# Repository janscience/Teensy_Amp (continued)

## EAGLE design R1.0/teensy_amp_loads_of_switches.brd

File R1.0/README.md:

# TeensyAmp R1.0

by [Stefan Mucha](https://github.com/muchaste)

with support by [Avner Wallach](https://github.com/avner-wallach) and
[Jan Benda](https://github.com/janscience).

The input signals are processed in the following way:

- simple RC high-pass filtering, cutoff frequencies selectable via
  S1/S2 switches (0.1Hz, 100Hz, 300Hz)

- amplification ([Analog devices
  AD8224HACPZ-WP](https://www.analog.com/media/en/technical-documentation/data-sheets/AD8224.pdf)),
  gain selectable via S3/S4 switches (x5, x30, x180)

- low-pass filtering ([Analog devices
  OP2177ARZ](https://www.analog.com/media/en/technical-documentation/data-sheets/op1177_2177_4177.pdf)),
  cutoff frequencies selectable via S5/S6 switches (10kHz, 33kHz)

- a voltage-divider generates the 1.66V reference/ground potential ([Analog devices OP1177R](https://www.analog.com/media/en/technical-documentation/data-sheets/op1177_2177_4177.pdf))

How to configure gain and filter settings is described in
[AmplifierConfiguration.pdf](AmplifierConfiguration.pdf).

## Circuit

- [EAGLE circuit board](teensy_amp_loads_of_switches.brd)
- [EAGLE design rule](teensy_amp_loads_of_switches.dru)
- [EAGLE schematics file](teensy_amp_loads_of_switches.sch)
- [EAGLE autorouter statistics](teensy_amp_loads_of_switches.pro)

| Name1 | Name2 | Potential |
| :---- | :---- | --------: |
| VCC   | VPP   | 5V        |
| VDD   | VSS   | 0V        |
| GND1  | GND2  | 1.66V     |

## Pins

Input pins to the left, "TeensyAmp R1.0" bottom right.

### JP1 and JP2: differential inputs 1 and 2

| pin  | signal | position |
| ---: | :----  | :------- |
|    1 | IN+    | bottom   |
|    2 | IN-    | top      |

### JP3: output signals and power fowarding

| pin  | signal     | position     |
| ---: | :--------  | :----------- |
|    1 | OUT2 (JP2) | top left     |
|    2 | OUT1 (JP1) | top right    |
|    3 | VPP        | bottom left  |
|    4 | VSS        | bottom right |

- connect the amplified signals OUT1 and OUT2 to analog inputs of
  the Teensy.
- VPP and VSS could be used to power the Teensy.
- VSS does not need to be connected to AGND or GND of the Teensy!

### JP4: power input and reference generation

| pins | signal | position |
| ---: | :----- | :------- |
| 1, 2 | VCC    | top      |
| 3, 4 | VDD    | center   |
| 5, 6 | GND1   | bottom   |

- right column: VCC and VDD is used to create GND1 (1.66V).
- left column: input power and GND for the amplifier. Connected to JP5.
- when using a single amplifier,
  - connect power to both columns, in order to drive both the
    generation of the GND1 potential (right column) and the amplifier
    (left column).
  - connect the generated GND1 from the right column to GND1 of the
    left column by means of a jumper.
- additional slave amplifiers do not need to generate their GND1
  potential themselves. They receive it from the JP5 pins of the
  master amplifier on the left column of the JP4 pins.

### JP5: power forwarding

| pin  | signal      | position |
| ---: | :---------- | :------- |
|    1 | VPP = VCC   | top      |
|    2 | VSS = VDD   | center   |
|    3 | GND2 = GND1 | bottom   |

- connect these to the left column of JP4 of a another amplifier in
  order to provide power and reference. The other amplifier then does
  not need any power input to the right column of JP4.
- if only a single amplifier is used, these pins are not used.

## Filter

For selecting high- and low-pass filter settings see
[AmplifierConfiguration.pdf](AmplifierConfiguration.pdf).

### High-pass filter

| S1/S2 switch/jumper position | R1      | Ci    | tau    | fcutoff |
| :--------------------------- | ------: | ----: | -----: | ------: |
| p1 (upper jumper right)      | 100kOhm | 15uF  | 1.5s   | 0.1Hz   |
| p2 (upper jumper left)       | 100kOhm | 15nF  | 1.5ms  | 106Hz   |
| p3 (upper jumper cable left) | 100kOhm | 5.6nF | 0.56ms | 283Hz   |

### Low-pass filter

| S5/S6 switch position | fcutoff |
| :-------------------- | ------: |
| p1 (left)             |  7kHz   |
| p2 (right)            | 33kHz   |

### Filter tests

In files [`tests/filter-*.wav`](tests) a 23mV signal was sampled with
100kHz and its frequency was increased as follows: 10Hz, 12.5Hz, 16Hz,
20Hz, 25Hz, 31.5Hz, 40Hz, 50Hz, 63Hz, 80Hz, 100Hz, 125Hz, 160Hz,
200Hz, 250Hz, 315Hz, 400Hz, 500Hz, 630Hz, 800Hz, 1000Hz, 1250Hz,
1600Hz, 2000Hz, 2500Hz, 3150Hz, 4000Hz, 5000Hz, 6300Hz, 8000Hz,
10kHz, 12.5kHz, 16kHz, 20kHz.

100Hz high-pass, 7kHz low-pass:

100Hz high-pass, 33kHz low-pass:

300Hz high-pass, 33kHz low-pass:

0.1Hz high-pass, 33kHz low-pass:

These plots were generated via
```
python3 ~/Arduino/libraries/TeeRec/extras/viewwave.py -s -c 0 -t 23 -a ../tests/filter-300Hz-33kHz-gain30-23mV.wav
```

## Gains and clipping

For selecting gains see
[AmplifierConfiguration.pdf](AmplifierConfiguration.pdf).

| S3/S4 switch position | gain |
| :-------------------- | ---: |
| p1 (left)             |   x5 |
| p2 (center)           |  x30 |
| p3 (right)            | x180 |

### Gain tests

In files [`tests/gain*.wav`](tests) a sinewave of a 630Hz was
amplified and recorded with both channels.

120mV rms amplitude (340mV p-p):

23mV rms amplitude (65mV p-p):

3.8mV rms amplitude (10.7mV p-p):

Nicely amplified, with a gain that seems a bit higher than specified.

These plots were generated via
```
python3 ~/Arduino/libraries/TeeRec/extras/viewwave.py -o 0.1 -t 0.005 -g 30 -s  ../tests/gain30-23mV.wav
```

### Clipping tests

In files [`tests/clipping-gain*-*mV-step*mV.wav`](tests) the amplitude
of a 630Hz signal was increased from a start voltage in steps as
specified in the file name. Shown is the voltage as the Teensy records
it (0-3.3V).

*The signals are clipped at the bottom at about 680mV!*

This is independent on gain. Also, it does not matter whether the
amplifier is powered by 5V or 3.3V.

These plots were generated via
```
python3 ~/Arduino/libraries/TeeRec/extras/viewwave.py -s -c 0 -t 10 -r -g 1 ../tests/clipping-gain30-20mV-step1mV.wav
```

## Power consumption

### Powered by 5V (power bank)

| Configuration     | Voltage | Current | Power | Run time |
| :---------------- | ------: | ------: | ----: | -------: |
| Amplifier         | 5V      | 11.4mA  |  57mW |  543h    |
| Teensy 3.5        | 5V      |  75mA   | 370mW |   82h    |
| Teensy + SD       | 5V      | 103mA   | 515mW |   60h    |
| Teensy + Amp      | 5V      |  87mA   | 433mW |   71h    |
| Teensy + Amp + SD | 5V      | 115mA   | 575mW |   54h    |

The last colum is the run time to be expected for a 10Ah battery (10Ah
times 3.7V LiPo voltage divided by 5.1V output voltage times 85%
efficiancy (=0.62) divided by current).

The amplifier takes just 11.5mA (57mW).

The Teensy consumes about seven to ten (with SD card writes) times
more power than the amplifier.

If we want to cut power consumption, we need to cut it on the Teensy!

### Powered by 3.3V

| Configuration     | Voltage | Current | Power |
| :---------------- | ------: | ------: | ----: |
| Amplifier         | 3.3V    | 6.5mA   |  21mW |
| Teensy 3.5        | 3.3V    |  68mA   | 225mW |
| Teensy + SD       | 3.3V    |  96mA   | 315mW |
| Teensy + Amp      | 3.3V    |  75mA   | 249mW |
| Teensy + Amp + SD | 3.3V    | 102mA   | 336mW |

This cuts down power consumption by almost a factor of two.  We should
power the system directly from the LiPo battery and not over the 5V
USB voltage.

## SD write artifacts

The files [`tests/sdwrites-gain*.wav`](tests) recorded 10s of
short-circuited inputs (zero signal).

With a sampling rate of 44kHz and two channels, an SD write occurs
every almost 200ms. This is visible in the traces as elevated noise
levels for about 2ms.

What is the reason for the irregularly appearing dips in the voltage?

These plots were generated via
```
python3 ~/Arduino/libraries/TeeRec/extras/viewwave.py -s -a -o 0.37 -t 0.03 ../tests/sdwrites-gain180-zero.wav
```

## Noise

Standard deviations in raw integers for each channel.

### 100kHz sampling rate, 12bit, 100Hz high-pass, 7kHz low pass, x30 gain

| convers  | sampling | avrg |   A1 |   A2 |
| :------- | :------- | ---: | ---: | ---: |
| veryhigh | veryhigh |    1 |  3.0 |  2.9 |
| veryhigh | veryhigh |    4 |  6.6 |  6.8 |
| veryhigh | veryhigh |    8 |  2.1 |  2.3 |
| veryhigh | high     |    1 |  4.5 |  4.4 |
| veryhigh | high     |    4 |  1.7 |  3.1 |
| veryhigh | high     |    8 |  5.4 |  5.8 |
| veryhigh | med      |    1 |  2.5 |  2.2 |
| veryhigh | med      |    4 |  3.3 |  3.5 |
| veryhigh | med      |    8 |  2.5 |  2.9 |
| veryhigh | low      |    1 |  5.9 |  5.9 |
| veryhigh | low      |    4 |  3.0 |  3.0 |
| veryhigh | low      |    8 |  4.6 |  4.6 |
| veryhigh | verylow  |    1 |  3.5 |  3.1 |
| veryhigh | verylow  |    4 |  1.9 |  1.8 |
| high     | veryhigh |    1 |  6.2 |  6.2 |
| high     | veryhigh |    4 |  4.8 |  4.9 |
| high     | high     |    1 |  6.1 |  6.0 |
| high     | high     |    4 |  1.6 |  1.6 |
| high     | med      |    1 |  2.8 |  2.7 |
| high     | med      |    4 |  4.2 |  4.3 |
| high     | low      |    1 |  4.9 |  4.8 |
| high     | low      |    4 |  1.7 |  1.7 |
| high     | verylow  |    1 |  4.0 |  4.0 |
| med      | veryhigh |    1 |  5.8 |  5.9 |
| med      | high     |    1 |  2.9 |  3.0 |
| med      | med      |    1 |  4.5 |  4.6 |
| med      | low      |    1 |  2.8 |  2.7 |
| med      | verylow  |    1 |  4.7 |  4.8 |

A good setting:

A bad setting:

### 20kHz sampling rate, 12bit, 100Hz high-pass, 7kHz low pass, x30 gain

| convers  | sampling | avrg |   A1 |   A2 |
| :------- | :------- | ---: | ---: | ---: |
| veryhigh | veryhigh |    1 |  3.3 |  3.3 |
| veryhigh | veryhigh |    4 |  4.2 |  3.1 |
| veryhigh | veryhigh |    8 |  1.9 |  1.9 |
| veryhigh | veryhigh |   16 |  3.5 |  3.8 |
| veryhigh | veryhigh |   32 |  1.9 |  1.8 |
| veryhigh | high     |    1 |  3.1 |  3.1 |
| veryhigh | high     |    4 |  2.5 |  2.4 |
| veryhigh | high     |    8 |  2.4 |  2.3 |
| veryhigh | high     |   16 |  2.8 |  1.9 |
| veryhigh | high     |   32 |  1.7 |  2.8 |
| veryhigh | med      |    1 |  3.4 |  3.5 |
| veryhigh | med      |    4 |  2.3 |  2.0 |
| veryhigh | med      |    8 |  1.7 |  1.5 |
| veryhigh | med      |   16 |  3.0 |  2.9 |
| veryhigh | med      |   32 |  1.9 |  2.0 |
| veryhigh | low      |    1 |  2.7 |  2.8 |
| veryhigh | low      |    4 |  2.0 |  2.0 |
| veryhigh | low      |    8 |  4.0 |  4.0 |
| veryhigh | low      |   16 |  1.4 |  1.3 |
| veryhigh | low      |   32 |  1.3 |  1.4 |
| veryhigh | verylow  |    1 |  3.3 |  3.1 |
| veryhigh | verylow  |    4 |  2.0 |  2.0 |
| veryhigh | verylow  |    8 |  1.4 |  1.4 |
| veryhigh | verylow  |   16 |  1.8 |  1.8 |
| veryhigh | verylow  |   32 |  2.7 |  2.1 |
| high     | veryhigh |    1 |  3.1 |  2.7 |
| high     | veryhigh |    4 |  2.1 |  2.0 |
| high     | veryhigh |    8 |  2.5 |  2.5 |
| high     | veryhigh |   16 |  1.4 |  1.4 |
| high     | veryhigh |   32 |  3.0 |  2.7 |
| high     | high     |    1 |  3.6 |  3.2 |
| high     | high     |    4 |  2.3 |  2.2 |
| high     | high     |    8 |  1.4 |  1.3 |
| high     | high     |   16 |  2.0 |  2.0 |
| high     | med      |    1 |  3.3 |  3.1 |
| high     | med      |    4 |  2.0 |  2.0 |
| high     | med      |    8 |  1.4 |  1.4 |
| high     | med      |   16 |  1.7 |  1.8 |
| high     | low      |    1 |  6.1 |  6.1 |
| high     | low      |    4 |  1.5 |  1.5 |
| high     | low      |    8 |  2.2 |  2.1 |
| high     | low      |   16 |  3.0 |  2.8 |
| high     | verylow  |    1 |  3.3 |  3.1 |
| high     | verylow  |    4 |  1.9 |  1.9 |
| high     | verylow  |    8 |  2.2 |  2.2 |
| high     | verylow  |   16 |  2.3 |  2.3 |
| med      | veryhigh |    1 |  2.4 |  2.3 |
| med      | veryhigh |    4 |  2.3 |  2.3 |
| med      | veryhigh |    8 |  2.1 |  2.1 |
| med      | veryhigh |   16 |  1.2 |  1.2 |
| med      | high     |    1 |  3.2 |  2.9 |
| med      | high     |    4 |  2.4 |  2.3 |
| med      | high     |    8 |  1.5 |  1.4 |
| med      | high     |   16 |  2.2 |  2.2 |
| med      | med      |    1 |  3.1 |  3.1 |
| med      | med      |    4 |  6.4 |  6.4 |
| med      | med      |    8 |  1.5 |  1.5 |
| med      | low      |    1 |  3.4 |  3.2 |
| med      | low      |    4 |  3.6 |  2.8 |
| med      | low      |    8 |  1.3 |  1.3 |
| med      | verylow  |    1 |  2.5 |  2.4 |
| med      | verylow  |    4 |  2.1 |  2.1 |
| med      | verylow  |    8 |  2.0 |  2.0 |

A good setting:

A bad setting:

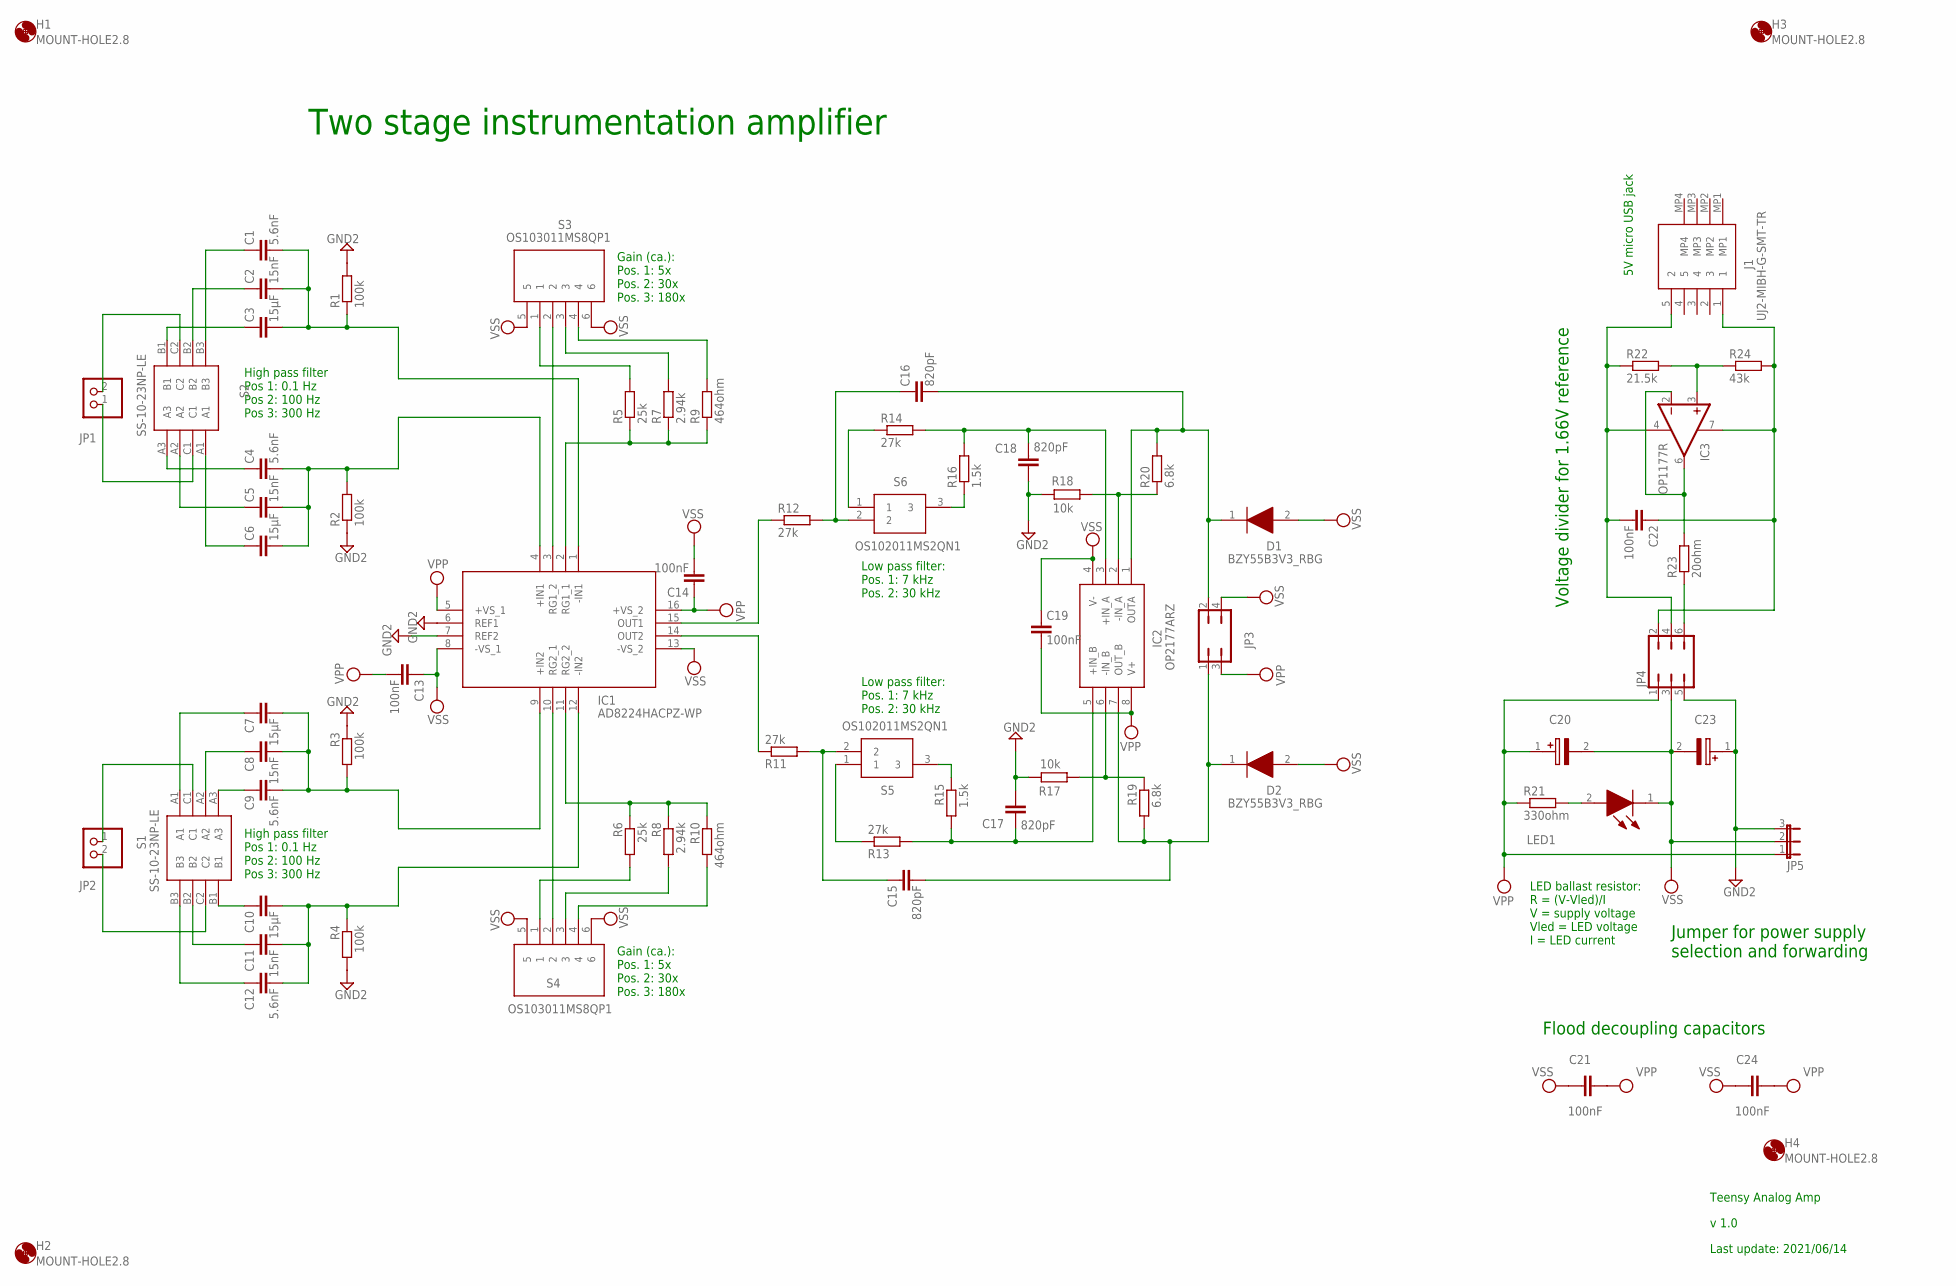
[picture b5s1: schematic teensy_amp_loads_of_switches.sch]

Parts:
C1, C4, C9, C12: 5.6nF; C0805
C2, C5, C8, C11: 15nF; C0805
C3, C6, C7, C10: 15µF; C0805
C13, C14, C19, C21, C22, C24: 100nF; C0805
C15, C16, C17, C18: 820pF; C0805
C20, C23: TAJA475K010RNJV; CAPPM3216X180N
D1, D2: BZY55B3V3_RBG; BZY55B3V3RBG
H1, H2, H3, H4: MOUNT-HOLE2.8; 2,8
IC1: AD8224HACPZ-WP; QFN65P400X400X100-16N
IC2: OP2177ARZ; SOIC127P600X175-8N
IC3: OP1177R; SOIC8
J1: UJ2-MIBH-G-SMT-TR; UJ2MIBHGSMTTR
JP1, JP2: PINHD-1X2; 1X02
JP3: JP2Q
JP4: JP3Q
JP5: JP2E; JP2
LED1: 150060RS75000; LEDC1608X80N
R1, R2, R3, R4: 100k; R0805
R5, R6: 25k; R0805
R7, R8: 2.94k; R0805
R9, R10: 464ohm; R0805
R11, R12, R13, R14: 27k; R0805
R15, R16: 1.5k; R0805
R17, R18: 10k; R0805
R19, R20: 6.8k; R0805
R21: 330ohm; R0805
R22: 21.5k; R0805
R23: 20ohm; R0805
R24: 43k; R0805
S1, S2: SS-10-23NP-LE; SS1023NPLE
S3, S4: OS103011MS8QP1
S5, S6: OS102011MS2QN1; OS102011MA1QN1

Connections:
GND2: C17.2, C18.2, C23.1 (+), IC1.6 (REF1), IC1.7 (REF2), JP4.5, JP5.3, R1.2, R2.1, R3.1, R4.2, R17.2, R18.2
unnamed: JP1.2, S2.C2
unnamed: JP1.1, S2.C1
unnamed: C16.1, R12.2, S6.2
unnamed: C4.1, S2.A3
unnamed: C5.1, S2.A2
unnamed: C6.1, S2.A1
unnamed: LED1.2 (A), R21.2
unnamed: C22.2, IC3.4 (V-), J1.5 (2), JP4.4, R22.1
unnamed: IC3.3 (+IN), R22.2, R24.1
unnamed: IC3.2 (-IN), IC3.6 (OUT), R23.2
unnamed: C22.1, IC3.7 (V+), J1.1, JP4.2, R24.2
unnamed: C3.1, S2.B1
unnamed: C1.1, S2.B3
unnamed: C4.2, C5.2, C6.2, IC1.4 (+IN1), R2.2
unnamed: C1.2, C2.2, C3.2, IC1.1 (-IN1), R1.1
unnamed: C2.1, S2.B2
unnamed: IC1.3 (RG1_2), S3.2
unnamed: IC1.15 (OUT1), R12.1
unnamed: IC2.2 (-IN_A), R18.1, R20.1
unnamed: C11.1, S1.B2
unnamed: C18.1, IC2.3 (+IN_A), R14.2, R16.2
unnamed: R6.2, S4.1
unnamed: R8.2, S4.3
unnamed: R10.2, S4.4
unnamed: IC1.11 (RG2_2), R6.1, R8.1, R10.1
unnamed: JP2.2, S1.C2
unnamed: JP2.1, S1.C1
unnamed: C9.1, S1.A3
unnamed: R5.2, S3.1
unnamed: R7.2, S3.3
unnamed: R9.2, S3.4
unnamed: IC1.2 (RG1_1), R5.1, R7.1, R9.1
unnamed: C8.1, S1.A2
unnamed: C7.1, S1.A1
unnamed: C10.1, S1.B1
unnamed: C12.1, S1.B3
unnamed: C7.2, C8.2, C9.2, IC1.9 (+IN2), R3.2
unnamed: C10.2, C11.2, C12.2, IC1.12 (-IN2), R4.1
unnamed: IC1.10 (RG2_1), S4.2
unnamed: JP4.6, R23.1
unnamed: R14.1, S6.1
unnamed: C16.2, D1.1 (K), IC2.1 (OUTA), JP3.2, R20.2
unnamed: R16.1, S6.3
unnamed: IC1.14 (OUT2), R11.1
unnamed: C17.1, IC2.5 (+IN_B), R13.2, R15.2
unnamed: IC2.6 (-IN_B), R17.1, R19.1
unnamed: C15.2, D2.1 (K), IC2.7 (OUT_B), JP3.1, R19.2
unnamed: R13.1, S5.1
unnamed: C15.1, R11.2, S5.2
unnamed: R15.1, S5.3
VPP: C13.2, C14.1, C19.2, C20.1 (+), C21.2, C24.2, IC1.5 (+VS_1), IC1.16 (+VS_2), IC2.8 (V+), JP3.3, JP4.1, JP5.1, R21.1
VSS: C13.1, C14.2, C19.1, C20.2 (-), C21.1, C23.2 (-), C24.1, D1.2 (A), D2.2 (A), IC1.8 (-VS_1), IC1.13 (-VS_2), IC2.4 (V-), JP3.4, JP4.3, JP5.2, LED1.1 (K), S3.5, S3.6, S4.5, S4.6

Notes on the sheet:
High pass filter Pos 1: 0.1 Hz Pos 2: 100 Hz Pos 3: 300 Hz
Gain (ca.): Pos. 1: 5x Pos. 2: 30x Pos. 3: 180x
Low pass filter: Pos. 1: 7 kHz Pos. 2: 30 kHz
Flood decoupling capacitors
5V micro USB jack
Jumper for power supply selection and forwarding
LED ballast resistor: R = (V-Vled)/I V = supply voltage Vled = LED voltage I = LED current
Teensy Analog Amp
v 1.0
Last update: 2021/06/14
Voltage divider for 1.66V reference
Two stage instrumentation amplifier

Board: 2 copper layers, 70 parts (2 on the bottom side), 53 nets, no tracks yet.

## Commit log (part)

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2021-11-15 Initial upload of pictures and schematics
2021-11-20 added teensy amp switches PCB.png
2021-11-20 READMEs for two revisions of the amp
2021-11-20 fixed pin markdown
2021-11-20 moved files to R1.0
2021-11-20 removed spaces from file names
2021-11-20 cropped images
2021-11-20 links to ICs
2021-11-20 added filter measurements
2021-11-20 added noise tests
2021-11-21 added clipping tests
2021-11-21 added sdwrite artifacts
2021-11-21 hint for low voltage clipping
2021-11-22 improved clipping plots
2021-11-22 more comments on clipping
2021-11-22 added 300Hz high-pass filter test
2021-11-22 added gain test data
2021-11-22 added gain examples
2021-11-22 organized R2 todos
2021-11-22 improved README
2021-11-22 some fixes
2021-11-23 Documentation for R1 amp configuration
2021-11-23 R1 picture added
2021-11-23 improved description of pin assignment
2021-11-23 larger pins image
2021-11-23 pins image further below
2021-11-24 more details on pins
2021-11-29 fixed runtime estimates
2021-11-29 added explanation to run time estimate
2022-04-30 [R2.0] new comments on 3.3V power supply
2022-05-10 comment on new OP amps for R2
2022-05-23 added link to fishfinder
2022-06-17 R3.0
2022-06-20 [R3.0] more gains
2022-06-28 [R3.0] circuit documentation
2022-06-28 [R3.0] cropped pcb
2022-06-29 [R3.0] added noise test for 441.kHz
2022-06-29 [R3.0] added noise test for 441.kHz and gain of 50
2022-06-29 [R3.0] new noise test for 441.kHz and gain of 50
2022-06-29 [R3.0] new sdwrites for gain of 50
2022-06-29 [R3.0] restored pcb description
2022-07-02 [R3] more capacities for highpass
2022-07-09 [R3.0] added images
2023-01-10 [R3] first tests of improved version
2023-01-10 [R3] added images of noise tests
2023-01-10 [R3] fixed images of noise tests
2023-01-13 [R3] sdwrite measurement with ldoaref
2023-01-14 a few more measurements
2023-01-14 documented sdwrite experiments
2023-01-16 [R3] removed R3 resistance from Teensy
2023-01-19 [R3] further tests with different higphpass and sampling rate
2023-01-19 [R3] updated 400kHz test
2023-01-20 [R3] externa power tests
2023-01-20 [R3] external power tests fixed image include
2023-01-21 more ideas in README
2023-01-23 [R3] new measurements
2023-01-23 [R3] test image arrangement
2023-01-23 [R3] test image arrangement 2
2023-01-23 [R3] test image arrangement 3
2023-01-24 [R3] added test with AGND
2023-01-25 [R3] clipping, filter and a gain test
2023-01-25 [R3] gain tests
2023-01-25 [R3] noise test at x870
2023-01-26 [R3] noise test at intermediate gains
2023-01-26 [R3] control sinewave
2023-01-26 [R3] sdwrite noise measured externally
2023-01-26 [R3] added conclusions to tests
2023-01-26 [R3] fixes
2023-02-01 [R3] fixed channel naming
2023-03-18 fixed image links
2023-04-04 [R4] more background infos
2023-04-05 [R4] 8 versus 16 channel
2023-06-07 updated power consumption
2023-06-21 pins
2023-06-27 notes on how to proceed with EVM
2023-06-28 gains and amplitudes
2023-07-02 [R4] added notes
2023-07-04 preamp
2023-07-04 preamp capacitors
2023-07-04 fixed preamp layout
2023-07-04 preamp with 220nF
2023-07-04 filter
2023-07-04 vref buffer
2023-07-04 small fixes
2023-07-06 updated pins
2023-07-06 push button
2023-07-06 fixed filter
2023-07-06 fixed preamp
2023-07-07 new measurements with properly windowed spectra
2023-07-07 fixed spectra
2023-07-07 fixed README
2023-07-07 fix spectra 2
2023-07-07 IO pins
2023-07-07 preamp and preampinv
2023-07-10 no lowpass necessary
2023-07-10 updated circuit
2023-07-10 added circuit
2023-07-10 highpass filter tests
2023-07-10 explored 40dB gain
2023-07-10 low pass at different gains
2023-07-10 low pass with 1 Ohm
2023-07-17 added eagle files
2023-07-17 cleaned up R4
2023-07-17 [R4] variants for components to test
2023-07-17 [R4] number of parts
2023-07-18 added pcb image
2023-07-28 [R4] 8 channel test
2023-07-28 [R4] fixed image link
2023-07-28 [R4] noise tests
2023-07-28 [R4] fixed noise image names
2023-07-28 [R4] added nonlinearity measurements of signal filter
2023-07-31 updated overview
2023-07-31 added clipping
2023-07-31 clipping tests
2023-07-31 fixing preamp tests
2023-08-01 [R4] evaluation
2023-08-01 [R4] improved spectra plots
2023-08-01 [R4] low-pass filter tests
2023-08-01 [R4] high-pass filter tests with preamp
2023-08-01 [R4] high-pass filter fix
2023-08-01 [R4] low-pass filter without preamp
2023-08-01 [R4] low-pass filter without preamp added images
2023-08-01 [R4] high-pass filter without preamp
2023-08-01 updated filter and preamp circuits
2023-08-02 circuit for 10x gain
2023-08-03 [R4] renamed variants to variants1
2023-08-03 [R4] added variants2
2023-08-03 [R4] linearity tests for variant2
2023-08-03 [R4] filter tests for variant2
2023-08-07 [R4] preamp with R1=100k
2023-08-07 [R4] filter with R1=100k
2023-08-07 [R4] filter with R1=1k
2023-08-07 [R4] updated filter circuit
2023-08-07 [R4] updated preamp circuits
2023-08-07 [R4.1] added R4.1
2023-08-07 [R4.1] fixed preaminv circuit
2023-08-07 [R4.1] explained circuit
2023-08-07 [R4.0] added filter measurements with low-pass
2023-08-07 [R4.0] fixed filter measurements with low-pass
2023-08-07 [R4.0] updated filter circuit
2023-08-07 [R4.0] updated preamp circuit
2023-08-08 [R4.0] measured power consumption
2023-08-09 [R4.0] fixed pins
2023-08-10 [R4] fixed pins
2023-08-10 [R4] improved pinouts
2023-08-11 [R4] 16 channels
2023-08-11 [R4] 16 channels in sync
2023-08-11 [R4.1] pinout
2023-08-15 dimensions
2023-08-15 [R4.1] pin update
2023-08-17 R4.2 circuits
2023-08-17 [R4.2] LED pin on 27
2023-08-17 added 4.1 to main page
2023-08-17 fixes
2023-08-18 [R40] image of board
2023-08-18 [R40] fixed image link
2023-09-08 [R4] added pcm1865 data sheet
2023-09-09 added images for the new R4.1 and R4.2 PCBs
2023-09-10 annotated R41 and R42 images
2023-09-11 updated R40 annotation
2023-09-11 added preamp tests
2023-09-11 filter measurement on single channel
2023-09-12 [R4.0] updated linearity spectra
2023-09-12 [R4.0] added OPA1622 data sheet
2023-09-15 [R4.0] CAN I/O in and out pins
2023-09-16 [R4.1] fixed IO pins
2023-09-16 [R4] fixed eagle links
2023-09-16 [R4] added TCAN data sheet
2023-09-16 [R4] CAN bus needs to be terminated
2023-10-21 sugestions for improving R41. and R4.2
2024-08-02 added missing pdfs
2024-08-02 [R4.2] added missing jpg
2024-08-02 [R4.1] added missing jpg
2024-08-02 [R4.1-R4.2] added missing jpgs
2024-08-02 [R4.x] fixed docs
2024-08-02 [R5.0] infos on the TI chip
2024-08-06 [R4.x] updated docs
2024-08-07 [R4.x] added pinput images
2024-08-07 [R4.1b] added pinout image
2024-08-07 [R4.1b] fixed pinout link
2024-08-07 [R4.1b] changed pdf to svg
2024-08-07 [R4.1b] added VBAT
2024-08-08 [R4.0] moved PCB image to README
2024-08-08 [doc] updated use cases
2024-08-10 [doc] link to TeeRec
2024-08-10 [R4.2b] added pinout desciption
2024-08-10 [R4.2b] removed VBAT
2024-08-10 [R4.1b] comment on DIP switches for device ID
2024-08-12 [R4.1b] update on device ID dips
2024-08-13 [R4.1b] added layout
2024-08-13 [R4.1b] added coin battery type
2024-08-13 [R4.1b] added preamp sketch and gain
2024-08-13 [R4.1b] moved DIP switch to other side
2024-08-13 [R4.1b] update
2024-08-13 [R4.2b] fixed title
2024-09-09 [R4.1b] new specs
2024-09-10 [R4.1] added links to isolated CAN bus chips
2024-09-10 [R4.1] added SD cards and USB ports to layout
2024-09-10 [R4.1] CAN bus back in Teensy pinput
2024-09-11 [R4.0] added data rates and SD speed class
2024-09-14 [R4.0] link to data rates tables in TeeRec
2024-09-15 [R4.1] only one external SD card slot
2024-09-15 [R4.1] description of device ID dip switches
2024-09-15 [R4.1] added DIP power to pinout
2024-09-15 [R4.1] fixed text
2024-09-30 [R4.1b] updated details on external devices, inclusively backup SD card
2024-10-01 [R4.1b] added notes on power switch, push-button and on-board temperature sensor
2024-10-01 [R4.1b] fixes
2024-10-01 [R4.1b] added isolated CAN bus
2024-10-01 [R4.1b] turned pinpout
2024-10-01 [R4.1b] updated layout
2024-10-01 [R4.1b] temperature sensor
2024-10-02 [R4.1b] improved pin colors
2024-10-02 [R4.1b] link out to IC drawings
2024-10-02 [R4.1b] specified connectors
2024-10-02 [R4.1] note on larger PCB dimensions
2024-10-02 [R4.1] small improvements
2024-10-11 [R4.1] added notes on rotary DIP switch and yet another temperature sensor
2024-11-05 powerbank runtime
2024-11-22 [R4.1] add real-time clock to PCB
2024-11-25 [R4.1-R4.2] added more power measurements
2024-11-25 [R4.1+R4.2] script for analysing power consumption
2024-11-27 [powerconsumption] compute averages
2024-11-27 [doc] added infos to power banks
2024-12-20 [docs] more power consumption measurements
2024-12-21 evaluated power consumption
2024-12-21 removed brand from tables
2025-01-17 [R4.1] notes on isolation tests
2025-01-18 [R4.1] note on real time clocks
2025-01-23 [R41] alternative connectors
2025-01-24 [R41] test measurements for grid configuration
2025-01-24 [R4.1] added analysis of power tests
2025-01-25 [R4.1] added note on low-pass filter
2025-01-27 [R4.1] added power test ananlysis
2025-01-27 [R4.1] fixed power test
2025-01-27 [R4.1] improved calculations
2025-04-07 hint for small 10Ah powerbank
2025-06-04 [R4.1] updated new design
2025-07-01 [R4.1b] updated RTC
2025-07-06 [R4.1b] added parts
2025-07-07 [R41] added parts
2025-07-09 [R41] added rotary switch
2025-07-10 [R41] added note on slide switch
2025-07-11 [R4.1b] another power switch
2025-07-12 [R4.1b] yet another power switch
2025-07-13 [R4.1b] finalized
2025-07-15 opa1662 is the op amp
2025-10-20 [R4.2b] updated docs to new version
2025-10-20 [R4.1b] updated docs to new version
2025-10-20 [R4.1b-R4.2b] updated docs to new version
2025-10-22 [R41] uodated layout image
2025-10-22 [R41] updated docu
2025-10-22 [R4142] updated docu
2025-10-28 [R4.1c] without onewire bus
2025-10-29 [R4.1-R4.2] added power consumption
2025-10-30 [R4.1] small fixes
2025-11-10 added power measurements
2025-11-24 [R41-R42] table with chargers
2025-11-28 [R5.0] circuit for differential preamp
2025-12-01 [R4.1-R4.2] more nodes on battery chargers
2025-12-01 [R4.1-R4.2] fixed table
2025-12-04 [R4.1-R4.2] updated power consumption
2025-12-11 [R4.1-R4.2] new measurements
2025-12-17 [R4.1-R4.2] power update
2026-03-28 [R5.0] updated circuits
2026-03-28 [R5.0] updated refamp
2026-03-29 [R5.0] renamed amplifier imagesto noninv
2026-03-29 [R5.0] restored inverted circuits
2026-03-29 [R5.0] added inverting amplifiers
2026-03-29 [R5.0] compacter circuits
2026-03-29 [R5.0] removed frame
2026-03-29 [R5.0] AREF bus
2026-03-29 [R5.0] jumper for voltage divider
2026-03-30 [R5.0] added comments on amplifier
2026-03-31 [R5.0] made proper differential amplifiers
2026-03-31 fixed opamp references
2026-03-31 [R5.0] updated opa1662 data sheet
2026-03-31 [R5.0] inverted amplifiers
2026-03-31 [R5.0] improved understanding of single-ended measurement
2026-03-31 [R5.0] signals go into minus inputs
2026-04-01 [R5.0] figured out input and output ranges of opa1662
2026-04-01 [R5.0] cleaned up circuits files
2026-04-02 [R5.0] update on power supply and voltage reference for opamps
2026-04-02 [R5.0] added dual voltage reference
2026-04-03 [R5.0] notes on voltage supply and voltage references
2026-04-06 [R5.0] changed to non-inverting amplifiers to get the averaged signal right
2026-04-07 [R5.0] separated VGND from VREF
2026-04-07 [R5.0] test results regarding VREF=1.6V
2026-04-07 [R5.0] added VREF IC
2026-04-07 [R5.0] smaller VREF IC
2026-04-08 [R5.0] updated VREF chip in circuit
2026-04-08 [R5.0] added 1.6V voltage reference data sheet
2026-04-08 [R5.0] C1 in front
2026-04-08 [R5.0] updated circuit
2026-04-09 [R5.0] fixed voltage divider
2026-04-10 [R5.0] added breaks in circuit
2026-04-12 [R5.0] siwth between differential andmonopolar measurements
2026-04-13 [R5.0] notes on resistances and VREF
2026-04-14 [R5.0] VGND from MICBIAS
2026-04-15 [R5.0] set ref opamp to VGND in single ended measurements
2026-04-15 [R5.0] 1k for VGND voltage divider
2026-04-23 [R5.0] changed voltage divider
2026-04-23 [R5.0] removed spines
2026-04-27 [R5.0] added pinout
2026-05-19 [R5.0] updated pinout to single TDM bus
2026-05-19 [R5.0] new board connector
2026-05-20 [R5.0] added EEPROM
2026-05-21 [R5.0] added micro USB
2026-05-21 [R5.0] updated pinout of IO pins
2026-05-26 [R5] added data sheets
2026-05-28 [R5.0] updated pinouts and preamp settings
